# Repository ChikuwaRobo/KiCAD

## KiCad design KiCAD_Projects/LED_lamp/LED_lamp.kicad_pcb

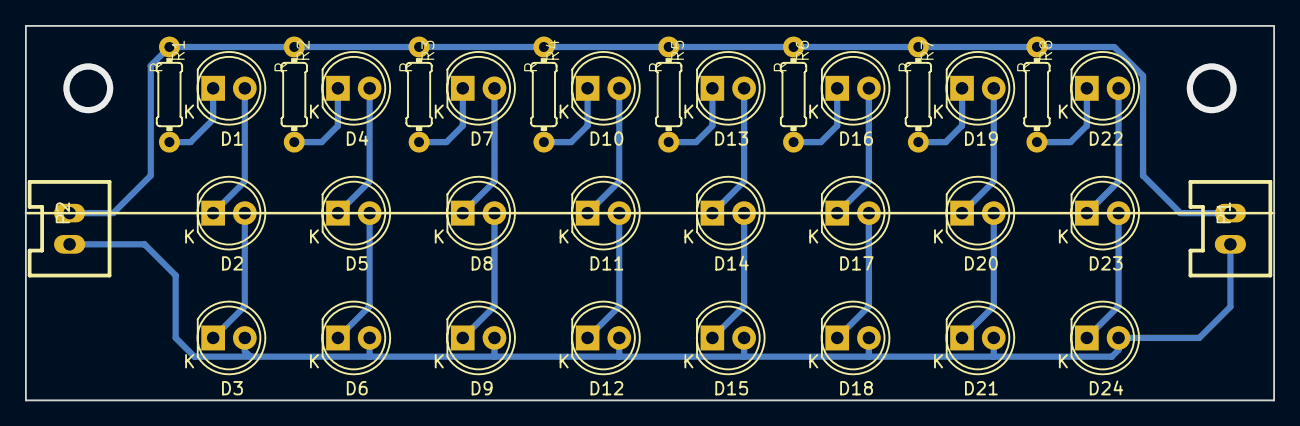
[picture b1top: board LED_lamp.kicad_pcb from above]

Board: 2 copper layers, 100.0 x 30.0 mm, 34 parts (0 on the bottom side), 26 nets.

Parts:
D1, D2, D3, D4, D5, D6, D7, D8, D9, D10, D11, D12, D13, D14, D15, D16, D17, D18, D19, D20, D21, D22, D23, D24: LED; LED-5MM
P1, P2: CONN_01X02; XA_2T
R1, R2, R3, R4, R5, R6, R7, R8: R; 0204_2f7

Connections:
+12V: P1.2, P2.2, R1.1, R2.1, R3.1, R4.1, R5.1, R6.1, R7.1, R8.1
GND: D3.2, D6.2, D9.2, D12.2, D15.2, D18.2, D21.2, D24.2, P1.1, P2.1
unnamed: D1.1, R1.2
unnamed: D1.2, D2.1
unnamed: D2.2, D3.1
unnamed: D4.1, R2.2
unnamed: D4.2, D5.1
unnamed: D5.2, D6.1
unnamed: D7.1, R3.2
unnamed: D7.2, D8.1
unnamed: D8.2, D9.1
unnamed: D10.1, R4.2
unnamed: D10.2, D11.1
unnamed: D11.2, D12.1
unnamed: D13.1, R5.2
unnamed: D13.2, D14.1
unnamed: D14.2, D15.1
unnamed: D16.1, R6.2
unnamed: D16.2, D17.1
unnamed: D17.2, D18.1
unnamed: D19.1, R7.2
unnamed: D19.2, D20.1
unnamed: D20.2, D21.1
unnamed: D22.1, R8.2
unnamed: D22.2, D23.1
unnamed: D23.2, D24.1

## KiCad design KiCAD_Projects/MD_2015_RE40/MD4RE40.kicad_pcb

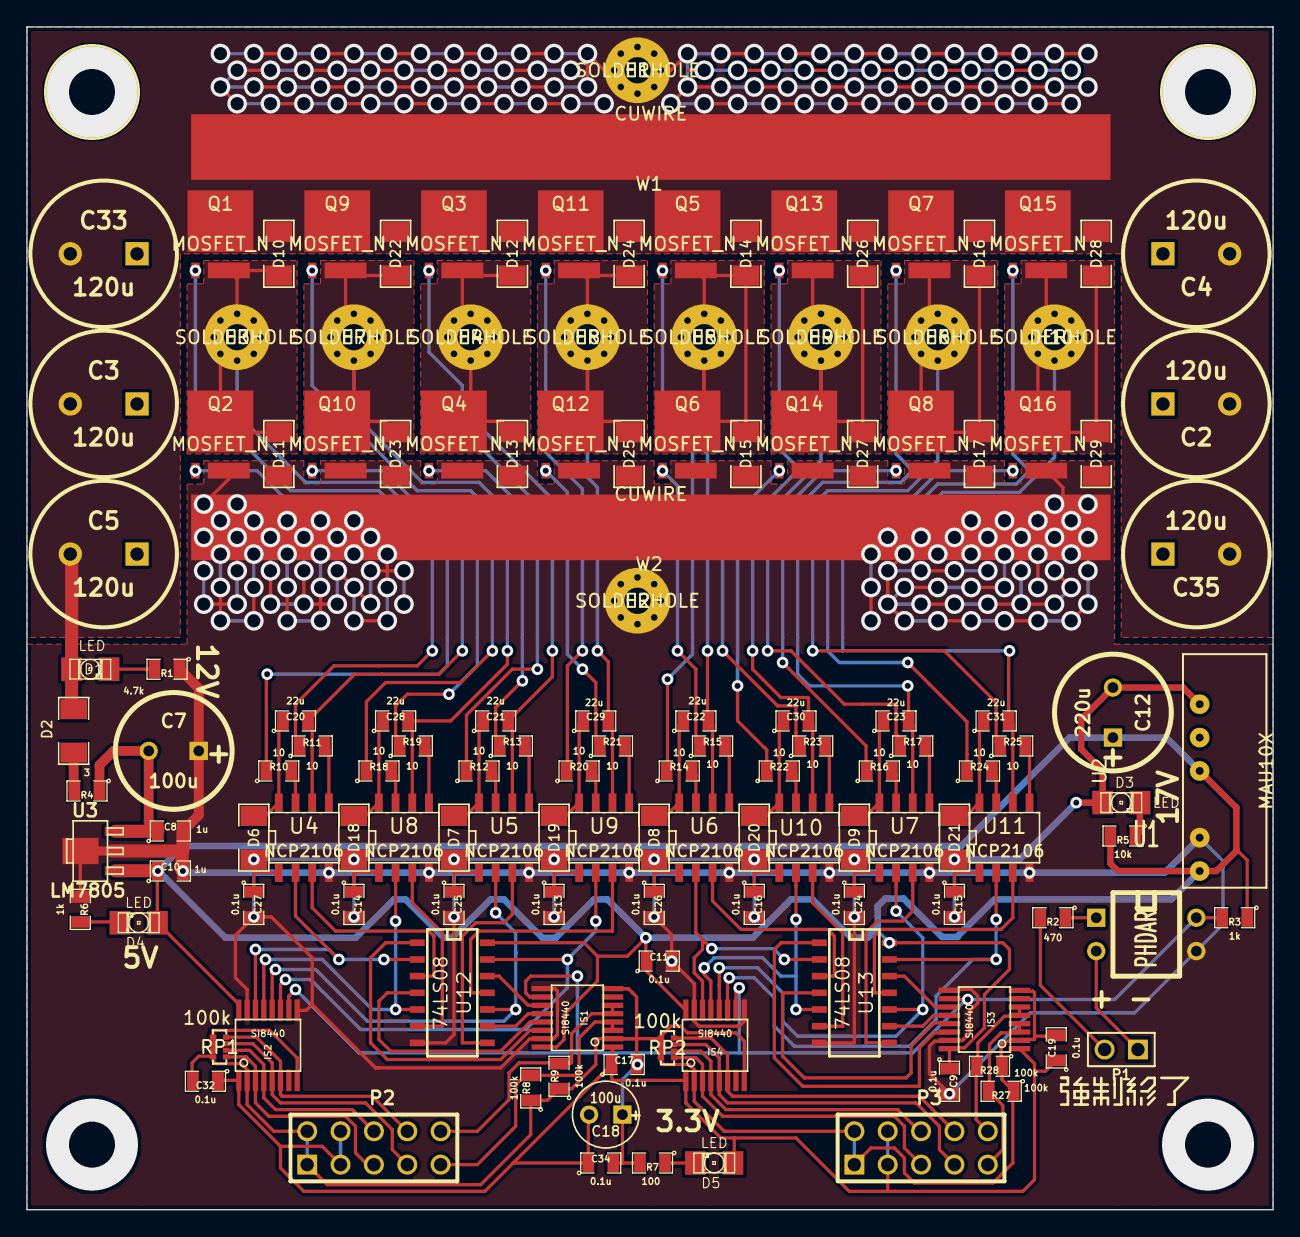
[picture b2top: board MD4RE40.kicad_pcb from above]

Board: 2 copper layers, 94.9 x 90.0 mm, 139 parts (0 on the bottom side), 100 nets.

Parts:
C2, C3, C4, C5, C33, C35: 120u; C2V10
C7: 100u; C1.5V8V
C8, C10: 1u; SM0805
C9, C11, C13, C14, C15, C16, C17, C19, C24, C25, C26, C27, C32, C34: 0.1u; SM0805
C12: 220u; C1.5V8V
C18: 100u; C1V5
C20, C21, C22, C23, C28, C29, C30, C31: 22u; SM0805
D1, D3, D4, D5: LED; LED-1206
D2, D6, D7, D8, D9, D10, D11, D12, D13, D14, D15, D16, D17, D18, D19, D20, D21, D22, D23, D24, D25, D26, D27, D28, D29: DIODE; SM1206
H1, H2, H3, H4, H5, H6, H7, H8, H9, H10: SOLDERHOLE; SolderHole
IS1, IS2, IS3, IS4: SI8440; ssop-16
P1: CONN_2; PIN_ARRAY_2X1
P2, P3: CONN_10; PIN_ARRAY_5x2
Q1, Q2, Q3, Q4, Q5, Q6, Q7, Q8, Q9, Q10, Q11, Q12, Q13, Q14, Q15, Q16: MOSFET_N; SuperSO8
R1: 4.7k; SM0805
R2: 470; SM0805
R3, R6: 1k; SM0805
R4: 3; SM0805
R5: 10k; SM0805
R7: 100; SM0805
R8, R9, R27, R28: 100k; SM0805
R10, R11, R12, R13, R14, R15, R16, R17, R18, R19, R20, R21, R22, R23, R24, R25: 10; SM0805
RP1, RP2: 100k; R_1005_Quad
U1: PHDARL; DIP-4__300
U2: MAU10X; MAU10x
U3: LM7805; sot89_reg
U4, U5, U6, U7, U8, U9, U10, U11: NCP2106; SO8E
U12, U13: 74LS08; SO14E
W1, W2: CUWIRE; CuWire_70mm

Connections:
12V: C7.2, C8.1, R4.1, U3.VI
17V: C12.2, C13.1, C14.1, C15.1, C16.1, C24.1, C25.1, C26.1, C27.1, D3.1, D6.1, D7.1, D8.1, D9.1, D18.1, D19.1, D20.1, D21.1, U2.6, U4.1, U5.1, U6.1, U7.1, U8.1, U9.1, U10.1, U11.1
+3.3V: C17.1, C18.2, C19.1, C32.1, C34.1, D5.1, IS1.1, IS2.1, IS3.1, IS4.1, P2.3, P2.4, P3.3, P3.4
+5V: C9.1, C10.1, C11.1, C12.1, D4.1, IS1.16, IS2.16, IS3.16, IS4.16, R3.1, R5.2, U2.1, U2.4, U3.VO, U12.14, U13.14
+12V: C2.2, C3.2, C4.2, C5.2, C33.2, C35.2, D1.1, D2.1, D10.2, D12.2, D14.2, D16.2, D22.2, D24.2, D26.2, D28.2, H1.1, Q1.D, Q3.D, Q5.D, Q7.D, Q9.D, Q11.D, Q13.D, Q15.D, W1.1
EN2: IS1.10, IS2.10, IS3.10, IS4.10, R3.2, U1.5
GND: C2.1, C3.1, C4.1, C5.1, C7.1, C8.2, C9.2, C10.2, C11.2, C13.2, C14.2, C15.2, C16.2, C24.2, C25.2, C26.2, C27.2, C33.1, C35.1, D11.1, D13.1, D15.1, D17.1, D23.1, D25.1, D27.1, D29.1, H2.1, IS1.9, IS1.15, IS2.9, IS2.15, IS3.9, IS3.15, IS4.9, IS4.15, Q2.S, Q4.S, Q6.S, Q8.S, Q10.S, Q12.S, Q14.S, Q16.S, R1.1, R6.1, U1.4, U2.2, U3.GND, U4.4, U5.4, U6.4, U7.4, U8.4, U9.4, U10.4, U11.4, U12.7, U13.7, W2.1
GNDA: C17.2, C18.1, C19.2, C32.2, C34.2, IS1.2, IS1.8, IS2.2, IS2.8, IS3.2, IS3.8, IS4.2, IS4.8, P2.1, P2.2, P3.1, P3.2, R7.2, R8.1, R9.1, R27.1, R28.1, RP1.5, RP1.6, RP1.7, RP1.8, RP2.5, RP2.6, RP2.7, RP2.8
IN_A0: IS2.14, U4.2, U12.2
IN_A1: IS2.13, U8.2, U12.5
IN_B0: IS2.12, U5.2, U12.10
IN_B1: IS2.11, U9.2, U12.13
IN_C0: IS4.14, U6.2, U13.2
IN_C1: IS4.13, U10.2, U13.5
IN_D0: IS4.12, U7.2, U13.10
IN_D1: IS4.11, U11.2, U13.13
unnamed: D4.2, R6.2
unnamed: IS1.14, U12.1
unnamed: IS1.13, U12.4
unnamed: IS1.12, U12.9
unnamed: IS1.11, U12.12
unnamed: P1.1, U1.2
unnamed: IS1.5, IS1.6, P2.10, R9.2
unnamed: IS1.3, IS1.4, P2.9, R8.2
unnamed: IS3.14, U13.1
unnamed: IS3.13, U13.4
unnamed: IS3.12, U13.9
unnamed: IS3.11, U13.12
unnamed: IS3.5, IS3.6, P3.10, R28.2
unnamed: IS3.3, IS3.4, P3.9, R27.2
unnamed: C21.1, D7.2, U5.8
unnamed: R12.2, U5.7
unnamed: R13.2, U5.5
unnamed: R15.2, U6.5
unnamed: C22.1, D8.2, U6.8
unnamed: R14.2, U6.7
unnamed: IS2.3, P2.5, RP1.4
unnamed: IS2.6, P2.8, RP1.1
unnamed: IS2.5, P2.7, RP1.2
unnamed: IS2.4, P2.6, RP1.3
unnamed: IS4.3, P3.5, RP2.4
unnamed: IS4.4, P3.6, RP2.3
unnamed: IS4.5, P3.7, RP2.2
unnamed: IS4.6, P3.8, RP2.1
unnamed: R10.2, U4.7
unnamed: R11.2, U4.5
unnamed: C20.1, D6.2, U4.8
unnamed: R22.2, U10.7
unnamed: R23.2, U10.5
unnamed: C30.1, D20.2, U10.8
unnamed: C31.1, D21.2, U11.8
unnamed: R24.2, U11.7
unnamed: R25.2, U11.5
unnamed: C28.1, D18.2, U8.8
unnamed: C23.1, D9.2, U7.8
unnamed: R16.2, U7.7
unnamed: R18.2, U8.7
unnamed: R17.2, U7.5
unnamed: C29.1, D19.2, U9.8
unnamed: R20.2, U9.7
unnamed: R21.2, U9.5
unnamed: R19.2, U8.5
unnamed: Q14.G, R23.1
unnamed: Q12.G, R21.1
unnamed: C30.2, D26.1, D27.2, H9.1, Q13.S, Q14.D, U10.6
unnamed: Q13.G, R22.1
unnamed: Q10.G, R19.1
unnamed: Q9.G, R18.1
unnamed: Q11.G, R20.1
unnamed: C29.2, D24.1, D25.2, H8.1, Q11.S, Q12.D, U9.6
unnamed: Q16.G, R25.1
unnamed: Q15.G, R24.1
unnamed: C31.2, D28.1, D29.2, H10.1, Q15.S, Q16.D, U11.6
unnamed: C28.2, D22.1, D23.2, H7.1, Q9.S, Q10.D, U8.6
unnamed: D3.2, R5.1
unnamed: Q4.G, R13.1
unnamed: D2.2, R4.2
unnamed: Q2.G, R11.1
unnamed: Q1.G, R10.1
unnamed: C20.2, D10.1, D11.2, H3.1, Q1.S, Q2.D, U4.6
unnamed: Q3.G, R12.1
unnamed: Q7.G, R16.1
unnamed: Q8.G, R17.1
unnamed: C23.2, D16.1, D17.2, H6.1, Q7.S, Q8.D, U7.6
unnamed: C21.2, D12.1, D13.2, H4.1, Q3.S, Q4.D, U5.6
unnamed: Q6.G, R15.1
unnamed: Q5.G, R14.1
unnamed: C22.2, D14.1, D15.2, H5.1, Q5.S, Q6.D, U6.6
unnamed: R2.1, U1.1
unnamed: P1.2, R2.2
unnamed: D5.2, R7.1
unnamed: D1.2, R1.2
~SD_A0: U4.3, U12.3
~SD_A1: U8.3, U12.6
~SD_B0: U5.3, U12.8
~SD_B1: U9.3, U12.11
~SD_C0: U6.3, U13.3
~SD_C1: U10.3, U13.6
~SD_D0: U7.3, U13.8
~SD_D1: U11.3, U13.11

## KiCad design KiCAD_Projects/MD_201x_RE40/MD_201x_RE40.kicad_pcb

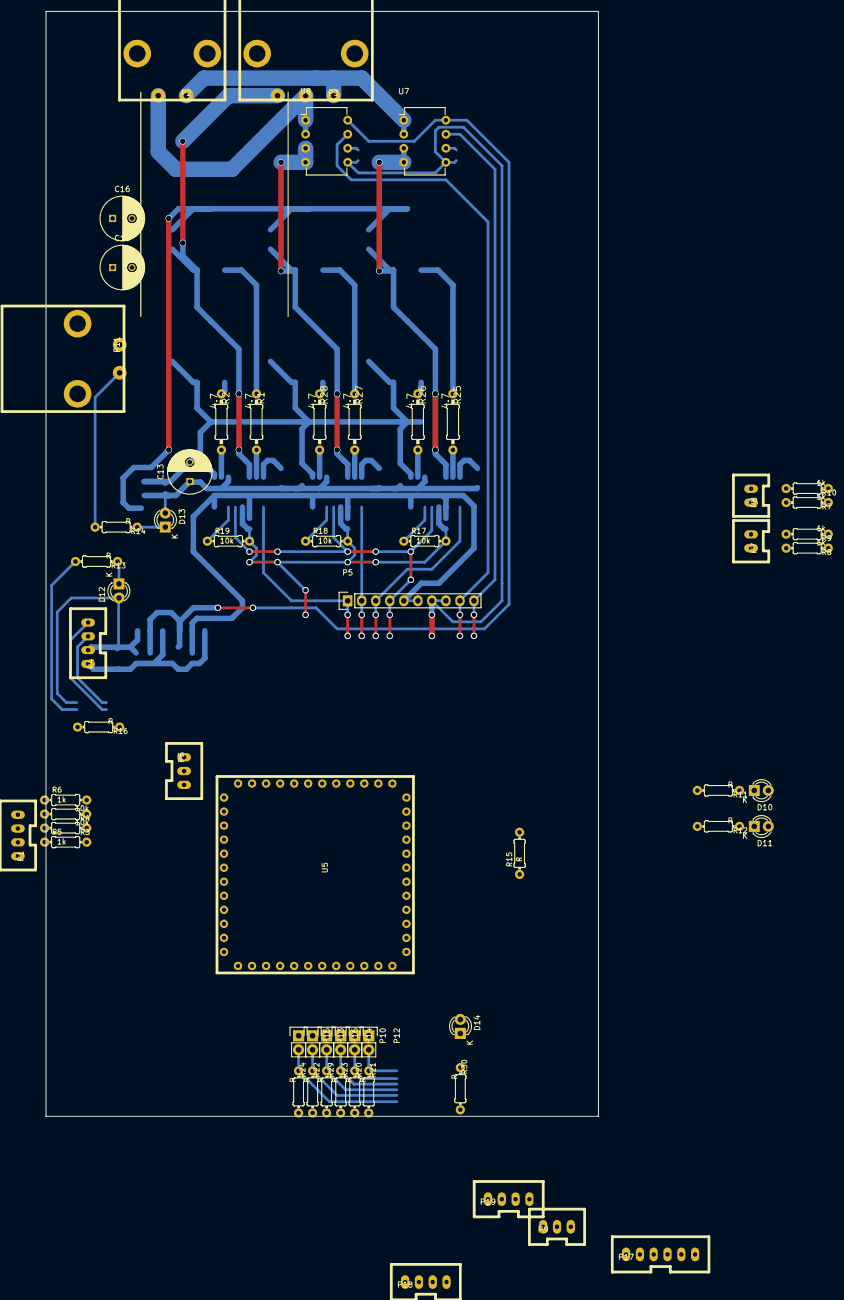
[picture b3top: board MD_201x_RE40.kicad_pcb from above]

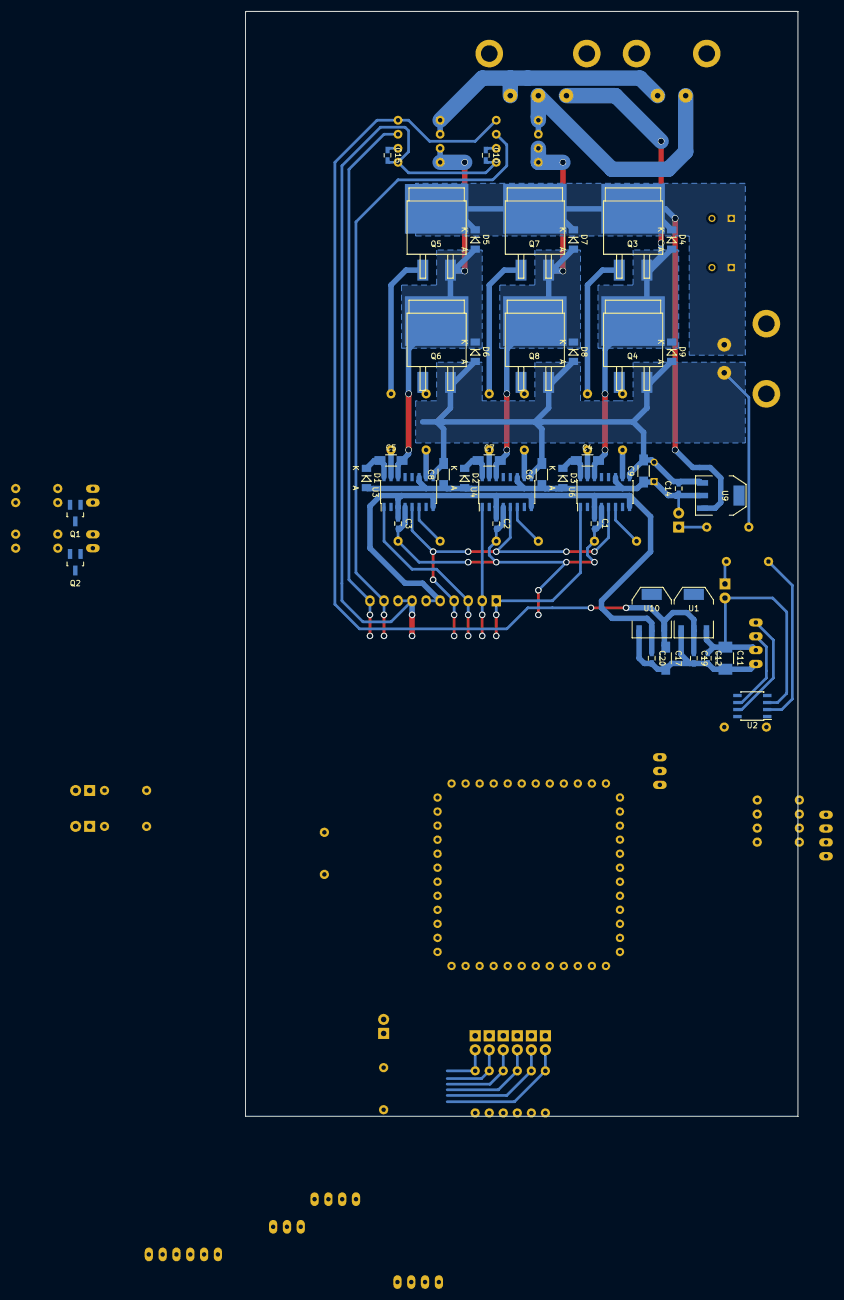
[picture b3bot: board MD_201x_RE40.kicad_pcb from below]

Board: 2 copper layers, 100.0 x 200.0 mm, 101 parts (41 on the bottom side), 74 nets.

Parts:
C1, C2, C3, C10, C12, C14, C15, C19, C20: C; C_0603_HandSoldering
C4, C5, C6, C7, C8, C9, C17: C; C_1206_HandSoldering
C11: C; C_1210_HandSoldering
C13, C16, C18: C; C_Radial_D8_L11.5_P3.5
D1, D2, D3, D4, D5, D6, D7, D8, D9: D; MiniMELF_Standard
D10, D11, D12, D13, D14: LED; LED-3MM
P1, P4, P18, P19: CONN_01X04; XA_4T
P2, P11: CONN_01X02; D-3200S_2
P3: CONN_01X03; D-3200S_3
P5: CONN_01X10; Socket_Strip_Straight_1x10
P6, P9: CONN_01X03; XA_3T
P7, P8: CONN_01X02; XA_2T
P10, P12, P13, P14, P15, P16: CONN_01X02; Socket_Strip_Straight_1x02
P17: CONN_01X06; XA_6T
Q1, Q2: Q_NMOS_SDG; SOT-23_Handsoldering
Q3, Q4, Q5, Q6, Q7, Q8: Q_NMOS_GDS; SOT-404
R1, R2, R25, R26, R27, R28: 4.7; 0207_2f10
R3, R4, R17, R18, R19: 10k; 0204_2f7
R5, R6, R7, R8, R9, R10: 1k; 0204_2f7
R11, R12, R13, R14, R15, R16, R20, R21, R22, R23, R24, R29, R30: R; 0204_2f7
U1, U9, U10: 7805; SOT-223_regul
U2: MCP2551; SOIC-8_3.9x4.9mm_Pitch1.27mm
U3, U4, U6: SI8234; SOIC-16_3.9x9.9mm_Pitch1.27mm
U5: STM32F103_48; PichConvertPCB_0.5-48
U7, U8: ACS714; DIP-8_W7.62mm

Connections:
+3V3: C1.1, C2.1, C3.1, C20.1, D11.2, P5.5, P5.6, P6.2, P9.2, P10.1, P12.1, P13.1, P14.1, P15.1, P16.1, P17.2, P18.2, P19.2, R7.1, R8.1, R9.1, R10.1, R15.2, U3.3, U3.8, U4.3, U4.8, U5.9, U5.24, U5.36, U5.48, U6.3, U6.8, U10.VO
+5V: C17.1, C19.1, D10.2, U1.VO, U7.8, U8.8, U10.VI
+12V: C11.1, C12.1, D12.2, P1.2, P4.2, R3.1, R4.1, U1.VI, U2.3
+15V: C6.1, C8.1, C9.1, C13.1, C14.1, D1.2, D2.2, D3.2, D13.2, U3.11, U4.11, U6.11, U9.VO
+BATT: C16.1, C18.1, D4.1, D5.1, D7.1, P11.1, Q3.2, Q5.2, Q7.2, U9.VI
/CAN_RX: U2.4, U5.32
/CAN_TX: U2.1, U5.33
/Current_A: P5.10, U5.18, U7.7
/Current_B: P5.9, U5.19, U8.7
/ENC_A: Q1.2, R7.2
/ENC_B: Q2.2, R8.2
/I2C2_SCL: P19.3, U5.21
/I2C2_SDA: P19.4, U5.22
/LIM_A: P7.2, R9.2
/PA8: D14.2, U5.29
/POT_A: P6.3, U5.10
/POT_B: P9.3, U5.11
/PWM_A: P5.3, U3.1, U5.42
/PWM_B: P5.2, U4.1, U5.43
/PWM_C: P5.1, U5.45, U6.1
/SPI2_MISO: P17.5, U5.27
/SPI2_MOSI: P17.6, U5.28
/SPI2_NSS: P17.3, U5.25
/SPI2_SCK: P17.4, U5.26
/TEMP_A_H: P14.2, R23.1, U5.12
/TEMP_A_L: P10.2, R20.1, U5.13
/TEMP_B_H: P15.2, R24.1, U5.14
/TEMP_B_L: P12.2, R21.1, U5.15
/TEMP_C_H: P16.2, R29.1, U5.16
/TEMP_C_L: P13.2, R22.1, U5.17
/USART1_RX: P18.3, U5.31
/USART1_TX: P18.4, U5.30
/~EN: P5.4, U3.5, U4.5, U5.46, U6.5
GND: C1.2, C2.2, C3.2, C10.2, C11.2, C12.2, C15.2, C17.2, C19.2, C20.2, P1.1, P4.1, P5.7, P5.8, P6.1, P7.1, P8.1, P9.1, P17.1, P18.1, P19.1, Q1.1, Q2.1, R11.2, R12.2, R13.2, R16.2, R17.2, R18.2, R19.2, R20.2, R21.2, R22.2, R23.2, R24.2, R29.2, R30.2, U1.GND, U2.2, U3.4, U4.4, U5.8, U5.23, U5.35, U5.47, U6.4, U7.5, U8.5, U10.GND
GNDPWR: C6.2, C8.2, C9.2, C13.2, C14.2, C16.2, C18.2, D6.2, D8.2, D9.2, P11.2, Q4.3, Q6.3, Q8.3, R14.2, U3.9, U4.9, U6.9, U9.GND
unnamed: C4.1, D3.1, U6.16
unnamed: C5.1, D1.1, U3.16
unnamed: C5.2, D5.2, D6.1, Q5.3, Q6.2, U3.14, U7.3, U7.4
unnamed: C7.1, D2.1, U4.16
unnamed: C7.2, D7.2, D8.1, Q7.3, Q8.2, U4.14, U8.3, U8.4
unnamed: C10.1, U8.6
unnamed: C15.1, U7.6
unnamed: D10.1, R11.1
unnamed: D11.1, R12.1
unnamed: D12.1, R13.1
unnamed: D13.1, R14.1
unnamed: D14.1, R30.1
unnamed: P1.3, R3.2, R5.1
unnamed: P1.4, R4.2, R6.1
unnamed: P4.3, U2.6
unnamed: P4.4, U2.7
unnamed: P8.2, R10.2
unnamed: Q1.3, R5.2
unnamed: Q2.3, R6.2
unnamed: Q3.1, R1.1
unnamed: Q4.1, R2.1
unnamed: Q5.1, R25.1
unnamed: Q6.1, R26.1
unnamed: Q7.1, R27.1
unnamed: Q8.1, R28.1
unnamed: R1.2, U6.15
unnamed: R2.2, U6.10
unnamed: R15.1, U5.7
unnamed: R16.1, U2.8
unnamed: R17.1, U3.6
unnamed: R18.1, U4.6
unnamed: R19.1, U6.6
unnamed: R25.2, U3.15
unnamed: R26.2, U3.10
unnamed: R27.2, U4.15
unnamed: R28.2, U4.10
OUT_A: P2.1, P3.1, U7.1, U7.2
OUT_B: P2.2, P3.2, U8.1, U8.2
OUT_C: C4.2, D4.2, D9.1, P3.3, Q3.3, Q4.2, U6.14

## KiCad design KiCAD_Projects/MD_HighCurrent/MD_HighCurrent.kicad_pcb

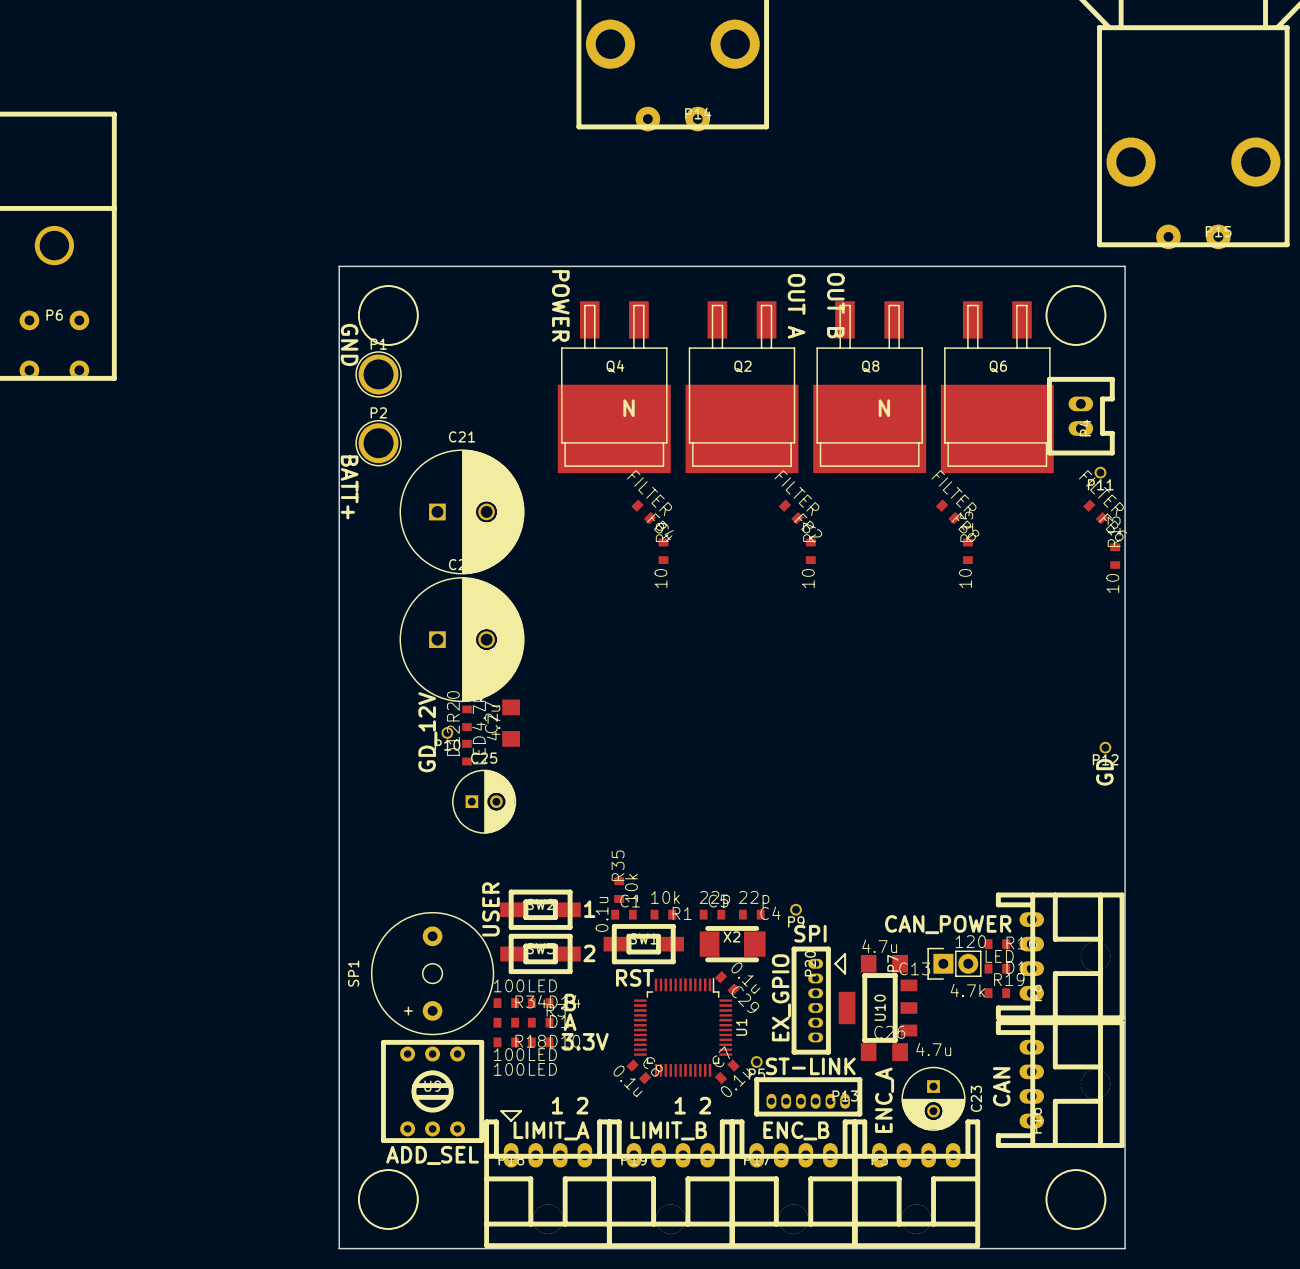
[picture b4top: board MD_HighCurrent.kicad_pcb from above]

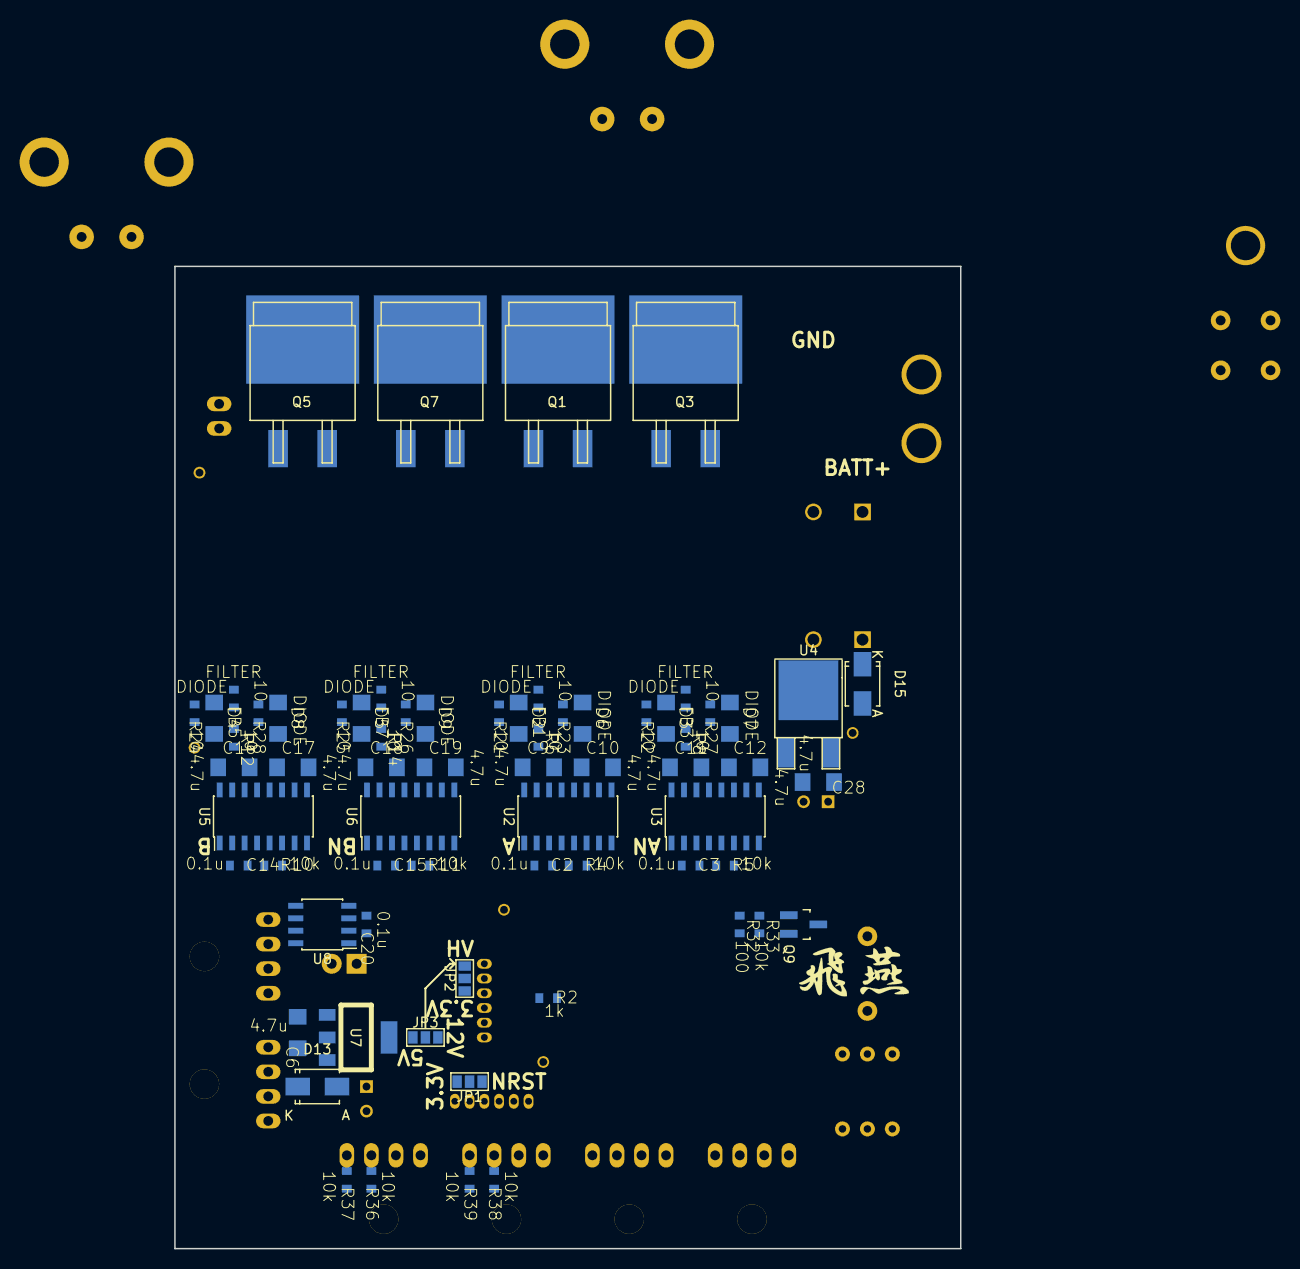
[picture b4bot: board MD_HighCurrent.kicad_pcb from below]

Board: 2 copper layers, 80.0 x 100.0 mm, 135 parts (69 on the bottom side), 106 nets, no tracks yet.

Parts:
C1, C2, C3, C7, C8, C14, C15, C20, C29: 0.1u; C1608_WP
C4, C5: 22p; C1608_WP
C6, C9, C10, C11, C12, C13, C16, C17, C18, C19, C26, C27, C28: 4.7u; C3216
C21, C22: 470u; C_Radial_D12.5_L25_P5
C23, C25: 100u; C_Radial_D6.3_L11.2_P2.5
D1, D10, D11, D12, D14: LED; C1608_WP
D2, D3, D4, D5, D6, D7, D8, D9: DIODE; C3216
D13, D15: DIODE; SMA_Standard
FB1, FB2, FB3, FB4, FB5, FB6, FB7, FB8: FILTER; C1608_WP
JP1, JP2, JP3: JUMPER3; GS3
LG1: user_logo; hien_mask
LG2: user_logo; hien_text
P1, P2: CONN_01X01; 1pin
P3, P8, P16, P17, P18, P19: CONN_01X04; XA_4LC
P4: CONN_01X02; XA_2T
P5, P9, P10, P11, P12: TST; testPin
P6: CONN_01X04; D-3500D_4S
P7: CONN_01X02; Pin_Header_Straight_1x02
P13, P20: CONN_01X06; ZH_6T
P14, P15: CONN_01X02; D-3200S_2L_PW
Q1, Q2, Q3, Q4, Q5, Q6, Q7, Q8: MOSFET_N; D2-PAK
Q9: MOSFET_N; SOT-23_Handsoldering
R1, R4, R5, R10, R11, R33, R35, R36, R37, R38, R39: 10k; C1608_WP
R2: 1k; C1608_WP
R3, R18, R32, R34: 100; C1608_WP
R6, R7, R8, R9, R12, R13, R14, R15, R21, R22, R23, R24, R25, R26, R27, R28: 10; C1608_WP
R16: 120; C1608_WP
R19, R20: 4.7k; C1608_WP
SP1: SPEAKER; Buzzer_12x9.5RM7.6
SW1, SW2, SW3: SW_PUSH; RP_SMD_Button
U1: STM32F103_48; LQFP-48_7x7mm_Pitch0.5mm
U2, U3, U5, U6: SI8234; SOIC-16_3.9x9.9mm_Pitch1.27mm
U4: LM7812; TO-252-2Lead_regu
U7, U10: NCP1117ST33T3G; SOT-223_reg
U8: MAX3051; SOIC-8_3.9x4.9mm_Pitch1.27mm
U9: SW_ROTARY_16; rotary_0F
X2: CRYSTAL; ABM3_2pads

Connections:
+3.3V: C2.2, C3.2, C7.2, C8.2, C14.2, C15.2, C20.2, C26.1, C29.2, D10.1, JP1.3, JP2.1, P5.1, P18.2, P19.2, R1.1, R36.1, R37.1, R38.1, R39.1, U1.1, U1.9, U1.24, U1.36, U1.48, U2.3, U2.8, U3.3, U3.8, U5.3, U5.8, U6.3, U6.8, U8.3, U10.2
+5V: C13.1, JP3.1, P3.2, P17.2, U7.2, U10.3
+12V: D11.1, D13.1, P8.2, P16.2, SP1.1
+BATT: C21.1, C22.1, D15.1, P2.1, P4.2, P6.2, P6.4, Q1.D, Q3.D, Q5.D, Q7.D
/BOOT0: R2.2, U1.44
/BUZZER: R32.2, U1.18
/CANH: P8.3, P16.3, R16.1, U8.7
/CANL: P7.1, P8.4, P16.4, U8.6
/CAN_RX: U1.32, U8.4
/CAN_TX: U1.33, U8.1
/ENC_Aa: P3.3, R36.2, U1.10
/ENC_Ab: P3.4, R37.2, U1.11
/ENC_Ba: P17.3, R38.2, U1.16
/ENC_Bb: P17.4, R39.2, U1.17
/EXIO_0: P20.3, U1.41
/EXIO_1: P20.4, U1.40
/EXIO_2: P20.5, U1.39
/EXIO_3: P20.6, U1.38
/GD_12V: C25.1, C28.1, D12.1, P12.1, R21.1, R22.1, R23.1, R24.1, R25.1, R26.1, R27.1, R28.1, U4.VO
/LED_A: D14.1, U1.14
/LED_B: D1.1, U1.15
/LIMIT_A1: P18.3, U1.26
/LIMIT_A2: P18.4, U1.27
/LIMIT_B1: P19.3, U1.28
/LIMIT_B2: P19.4, U1.29
/MOTOR_EN: R35.2, U1.25, U2.5, U3.5, U5.5, U6.5
/NRST: C1.2, JP1.1, R1.2, SW1.2, U1.7
/OSC_IN: C4.1, U1.5, X2.1
/OSC_OUT: C5.1, U1.6, X2.2
/OUT_A: C9.2, P14.1, Q1.S, Q2.D, U2.14
/OUT_AN: C11.2, P14.2, Q3.S, Q4.D, U3.14
/OUT_B: C16.2, P15.1, Q5.S, Q6.D, U5.14
/OUT_BN: C18.2, P15.2, Q7.S, Q8.D, U6.14
/PWM_A: U1.45, U2.1
/PWM_AN: U1.46, U3.1
/PWM_B: U1.42, U5.1
/PWM_BN: U1.43, U6.1
/SEL_1: U1.19, U9.3
/SEL_2: U1.20, U9.1
/SEL_4: U1.21, U9.4
/SEL_8: U1.22, U9.6
/SW1: SW2.2, U1.12
/SW2: SW3.2, U1.13
/SWCLK: P13.3, U1.37
/SWDIO: P13.4, U1.34
/USART_RX: P13.6, U1.31
/USART_TX: P13.5, U1.30
GND: C1.1, C2.1, C3.1, C4.2, C5.2, C6.2, C7.1, C8.1, C13.2, C14.1, C15.1, C20.1, C23.2, C26.2, C29.1, P3.1, P8.1, P9.1, P13.1, P16.1, P17.1, P18.1, P19.1, P20.1, Q9.S, R2.1, R3.2, R4.2, R5.2, R10.2, R11.2, R18.2, R19.2, R33.2, R34.2, R35.1, SW1.1, SW2.1, SW3.1, U1.8, U1.23, U1.35, U1.47, U2.4, U3.4, U5.4, U6.4, U7.1, U8.2, U8.5, U8.8, U9.2, U9.5, U10.1
GNDPWR: C10.2, C12.2, C17.2, C19.2, C21.2, C22.2, C25.2, C27.2, C28.2, P1.1, P4.1, P6.1, P6.3, P11.1, Q2.S, Q4.S, Q6.S, Q8.S, R20.2, U2.9, U3.9, U4.GND, U5.9, U6.9
unnamed: C9.1, D2.2, U2.16
unnamed: C10.1, D6.2, U2.11
unnamed: C11.1, D3.2, U3.16
unnamed: C12.1, D7.2, U3.11
unnamed: C16.1, D4.2, U5.16
unnamed: C17.1, D8.2, U5.11
unnamed: C18.1, D5.2, U6.16
unnamed: C19.1, D9.2, U6.11
unnamed: C6.1, C23.1, D13.2, JP3.3, U7.3
unnamed: C27.1, D15.2, P10.1, U4.VI
unnamed: D1.2, R3.1
unnamed: D2.1, R21.2
unnamed: D3.1, R22.2
unnamed: D4.1, R24.2
unnamed: D5.1, R25.2
unnamed: D6.1, R23.2
unnamed: D7.1, R27.2
unnamed: D8.1, R28.2
unnamed: D9.1, R26.2
unnamed: D10.2, R18.1
unnamed: D11.2, R19.1
unnamed: D12.2, R20.1
unnamed: D14.2, R34.1
unnamed: FB1.1, R6.1
unnamed: FB1.2, Q1.G
unnamed: FB2.1, R7.1
unnamed: FB2.2, Q2.G
unnamed: FB3.1, R8.1
unnamed: FB3.2, Q3.G
unnamed: FB4.1, R9.1
unnamed: FB4.2, Q4.G
unnamed: FB5.1, R12.1
unnamed: FB5.2, Q5.G
unnamed: FB6.1, R13.1
unnamed: FB6.2, Q6.G
unnamed: FB7.1, R14.1
unnamed: FB7.2, Q7.G
unnamed: FB8.1, R15.1
unnamed: FB8.2, Q8.G
unnamed: JP1.2, P13.2
unnamed: JP2.2, P20.2
unnamed: JP2.3, JP3.2
unnamed: P7.2, R16.2
unnamed: Q9.D, SP1.2
unnamed: Q9.G, R32.1, R33.1
unnamed: R4.1, U2.6
unnamed: R5.1, U3.6
unnamed: R6.2, U2.15
unnamed: R7.2, U2.10
unnamed: R8.2, U3.15
unnamed: R9.2, U3.10
unnamed: R10.1, U5.6
unnamed: R11.1, U6.6
unnamed: R12.2, U5.15
unnamed: R13.2, U5.10
unnamed: R14.2, U6.15
unnamed: R15.2, U6.10

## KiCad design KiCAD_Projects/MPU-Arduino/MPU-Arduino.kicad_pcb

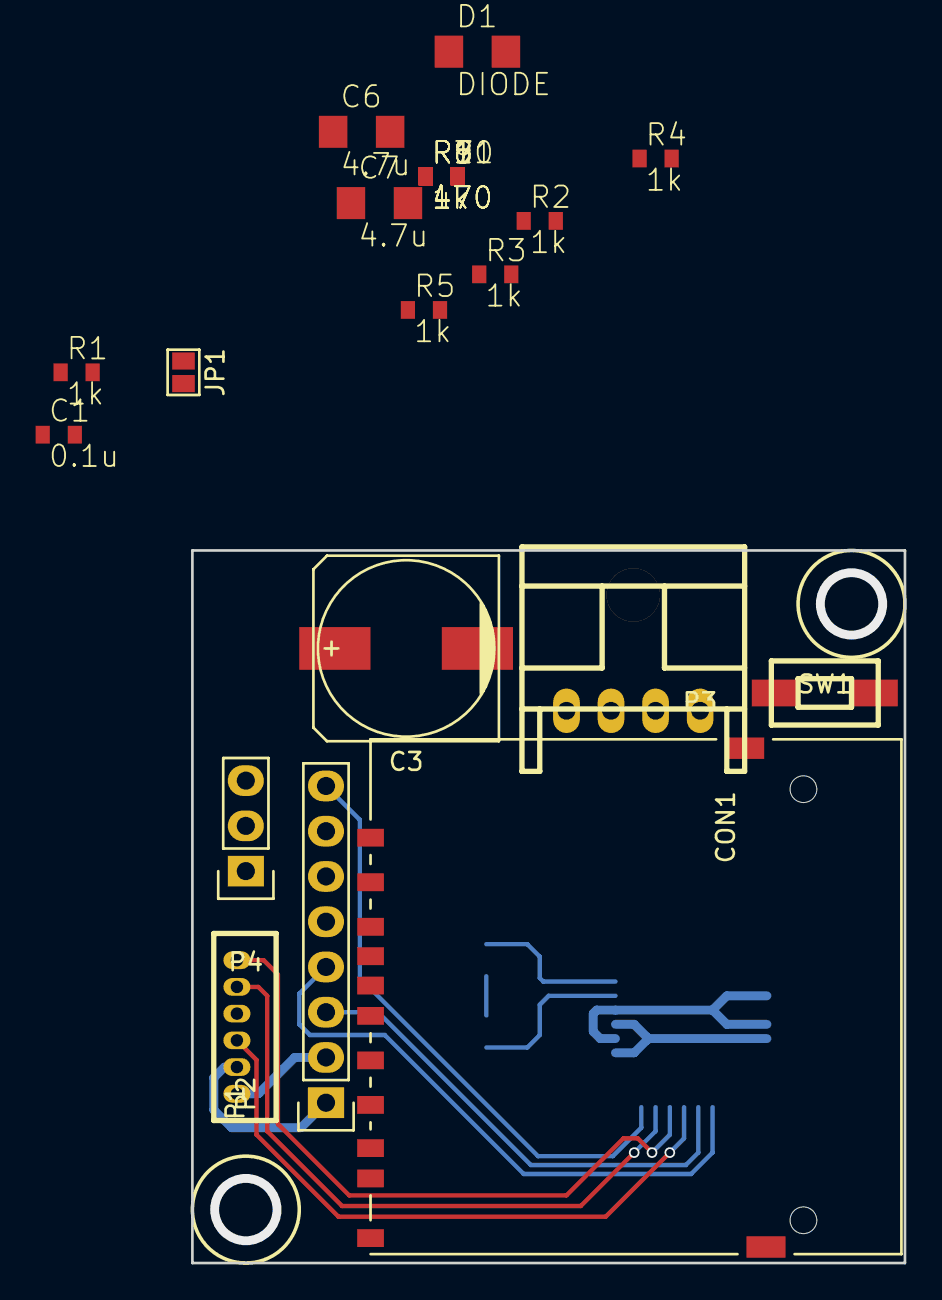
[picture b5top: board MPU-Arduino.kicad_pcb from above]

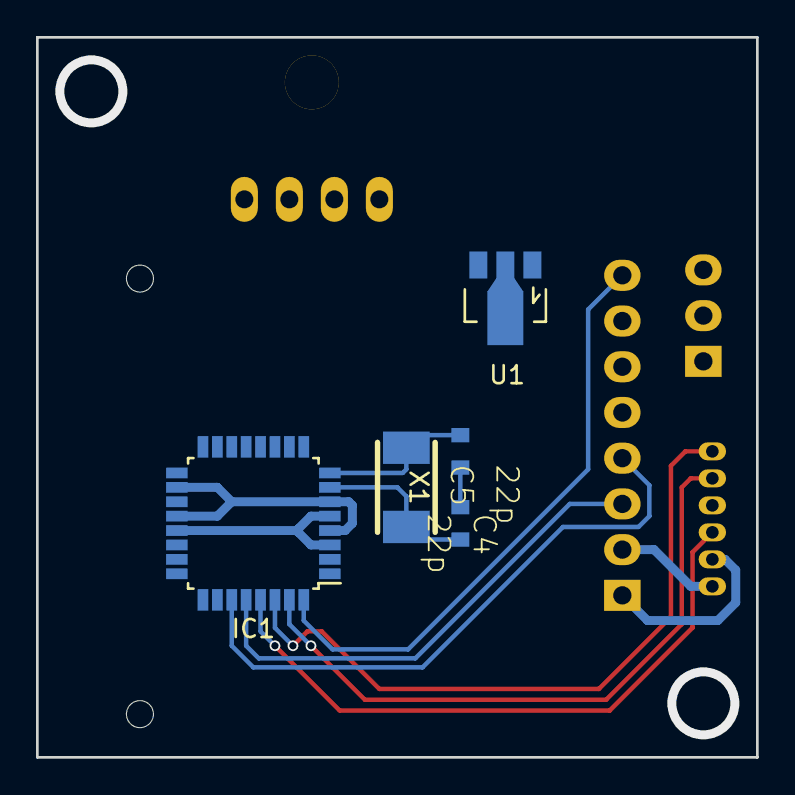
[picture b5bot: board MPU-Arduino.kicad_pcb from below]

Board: 2 copper layers, 40.0 x 40.0 mm, 28 parts (5 on the bottom side), 22 nets.

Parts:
C1: 0.1u; C1608_WP
C3: 0.22; c_elec_10x10
C4, C5: 22p; C1608_WP
C6, C7: 4.7u; C3216
CON1: SD_Card; SD_Card_Receptacle
D1: DIODE; C3216
IC1: ATMEGA328-A; LQFP-32_7x7mm_Pitch0.8mm
JP1: JUMPER; GS2
P1: CONN_01X08; Socket_Strip_Straight_1x08
P2: CONN_01X06; ZH_6T
P3: CONN_01X04; XA_4LC
P4: CONN_01X03; Pin_Header_Straight_1x03
R1, R2, R3, R4, R5, R7, R9, R11: 1k; C1608_WP
R6, R8, R10: 470; C1608_WP
SW1: SW_PUSH; RP_SMD_Button
U1: NCP1117ST33T3G; SOT89-3_Housing
X1: CRYSTAL; ABM3_2pads

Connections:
+3.3V: C7.1, CON1.4, U1.2
+5V: C1.1, C3.1, C6.1, D1.1, IC1.4, IC1.6, IC1.18, IC1.20, P1.1, P2.2, P4.3, R1.1, R3.2, R4.2, U1.3
/CLK: IC1.17, R10.2
/I2C_SCL: IC1.28, P1.3, R4.1
/I2C_SDA: IC1.27, P1.4, R3.1
/INT: IC1.32, P1.8
/IR: IC1.1, P4.1
/MISO: CON1.7, IC1.16
/MOSI: IC1.15, R6.2
/RST: IC1.29, P2.3, R1.2, SW1.1
/RX: IC1.30, P2.6, P3.3
/SS: IC1.14, R8.2
/TX: IC1.31, P2.5, P3.4
/Vsense: IC1.26, R2.1, R5.2
GND: C1.2, C3.2, C4.1, C5.1, C6.2, C7.2, CON1.3, CON1.6, CON1.12, CON1.13, IC1.3, IC1.5, IC1.21, JP1.2, P1.2, P2.1, P3.1, P4.2, R5.1, R7.2, R9.2, R11.2, SW1.2, U1.1
unnamed: C4.2, IC1.7, X1.1
unnamed: C5.2, IC1.8, X1.2
unnamed: CON1.1, R8.1, R9.1
unnamed: CON1.2, R6.1, R7.1
unnamed: CON1.5, R10.1, R11.1
unnamed: D1.2, P3.2, R2.2
unnamed: JP1.1, P1.7

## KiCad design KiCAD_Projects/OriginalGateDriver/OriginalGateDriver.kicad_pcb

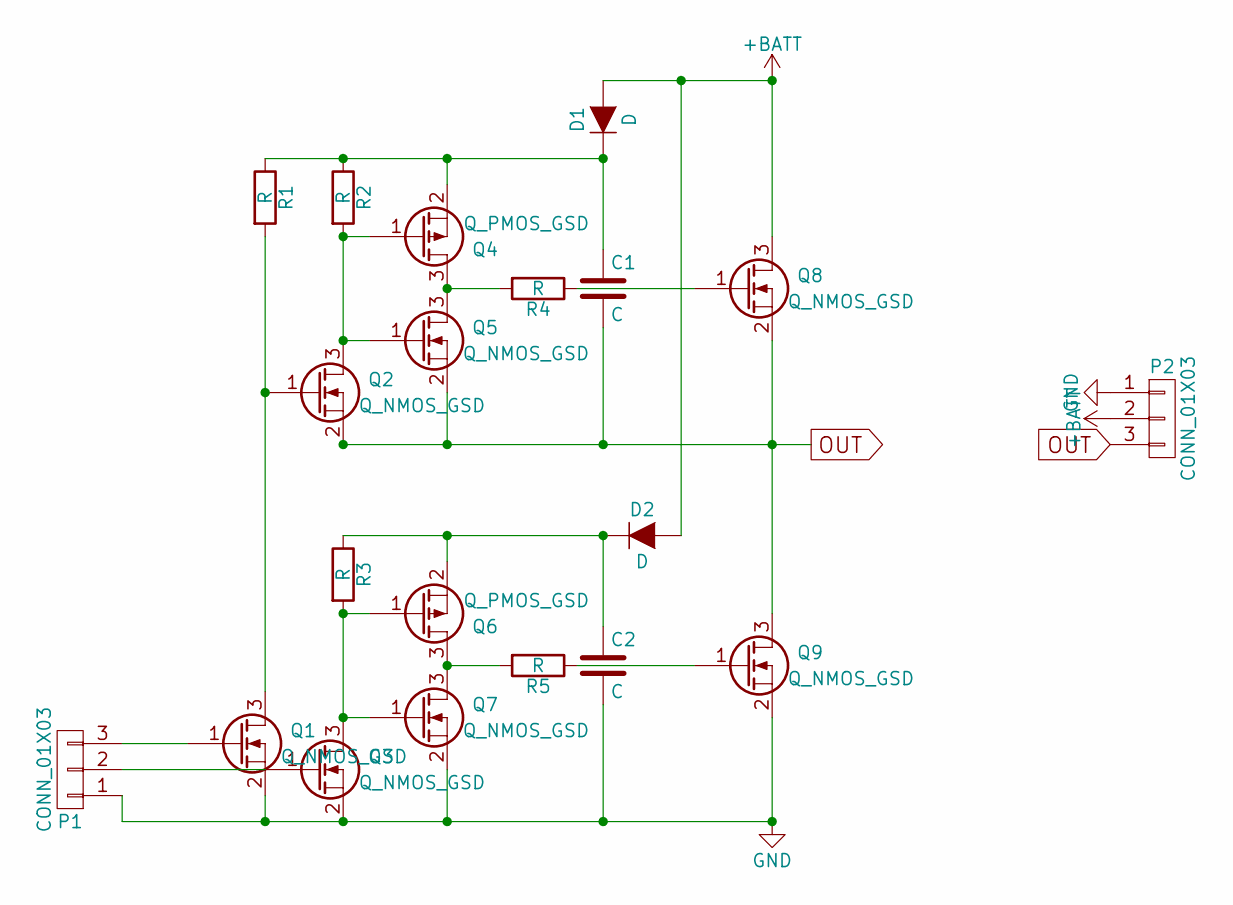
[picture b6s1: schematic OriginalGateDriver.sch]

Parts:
C1, C2: C; C_Radial_D5_L11_P2.5
D1, D2: D; Diode_DO-35_SOD27_Horizontal_RM10
P1, P2: CONN_01X03; XA_3T
Q1, Q2, Q3, Q5, Q7, Q8, Q9: Q_NMOS_GSD; SOT-23_Handsoldering
Q4, Q6: Q_PMOS_GSD; SOT-23_Handsoldering
R1, R2, R3, R4, R5: R; 0204_2f7

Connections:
+BATT: D1.2 (A), D2.2 (A), P2.2, Q8.3 (D)
GND: C2.2, P1.1, P2.1, Q1.2 (S), Q3.2 (S), Q7.2 (S), Q9.2 (S)
unnamed: C1.1, D1.1 (K), Q4.2 (S), R1.1, R2.1
unnamed: C2.1, D2.1 (K), Q6.2 (S), R3.1
unnamed: P1.2, Q3.1 (G)
unnamed: P1.3, Q1.1 (G)
unnamed: Q1.3 (D), Q2.1 (G), R1.2
unnamed: Q2.3 (D), Q4.1 (G), Q5.1 (G), R2.2
unnamed: Q3.3 (D), Q6.1 (G), Q7.1 (G), R3.2
unnamed: Q4.3 (D), Q5.3 (D), R4.2
unnamed: Q6.3 (D), Q7.3 (D), R5.2
unnamed: Q8.1 (G), R4.1
unnamed: Q9.1 (G), R5.1
OUT: C1.2, P2.3, Q2.2 (S), Q5.2 (S), Q8.2 (S), Q9.3 (D)

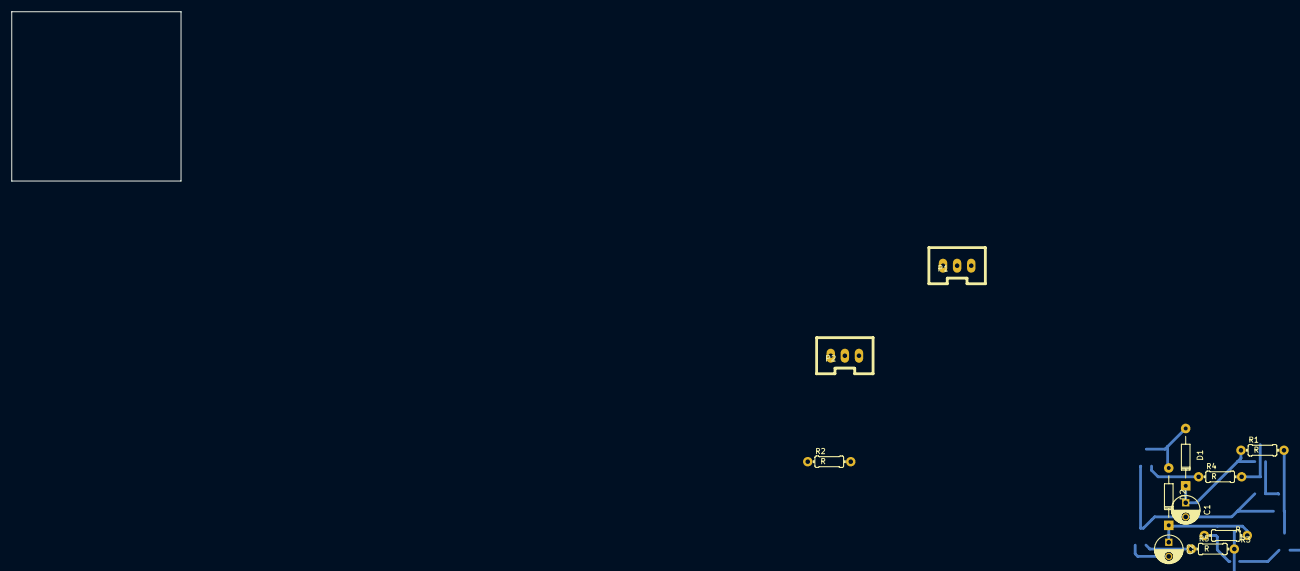
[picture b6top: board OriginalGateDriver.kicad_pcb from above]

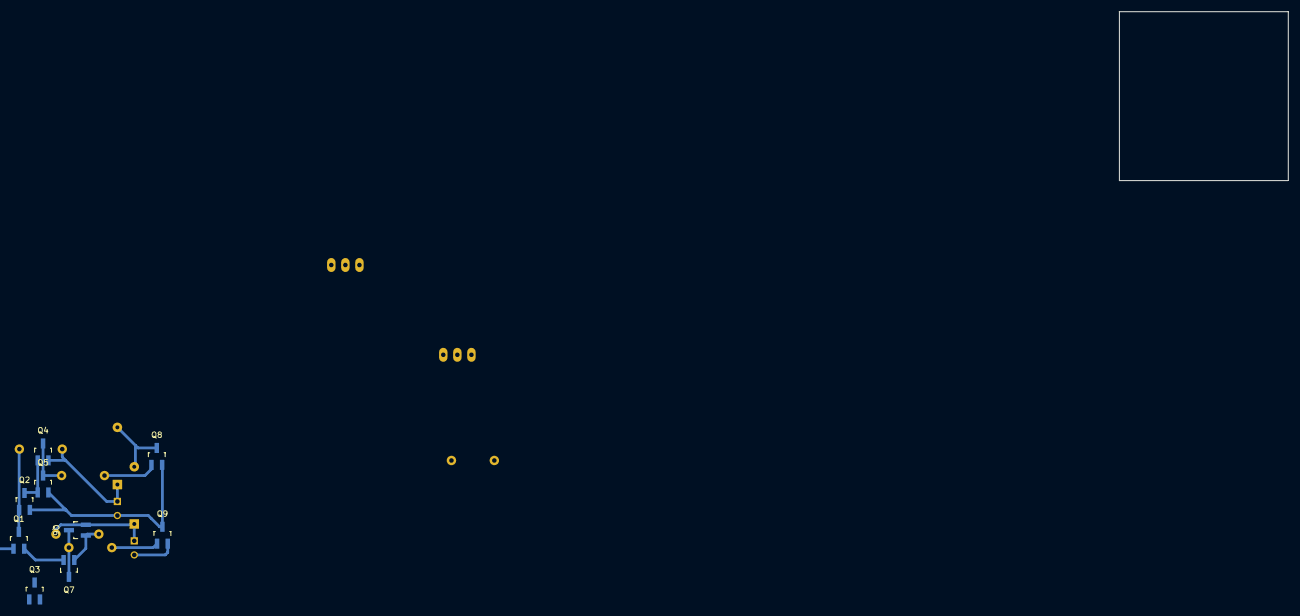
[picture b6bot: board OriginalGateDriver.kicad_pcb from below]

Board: 2 copper layers, 30.0 x 30.0 mm, 20 parts (9 on the bottom side), 14 nets.
